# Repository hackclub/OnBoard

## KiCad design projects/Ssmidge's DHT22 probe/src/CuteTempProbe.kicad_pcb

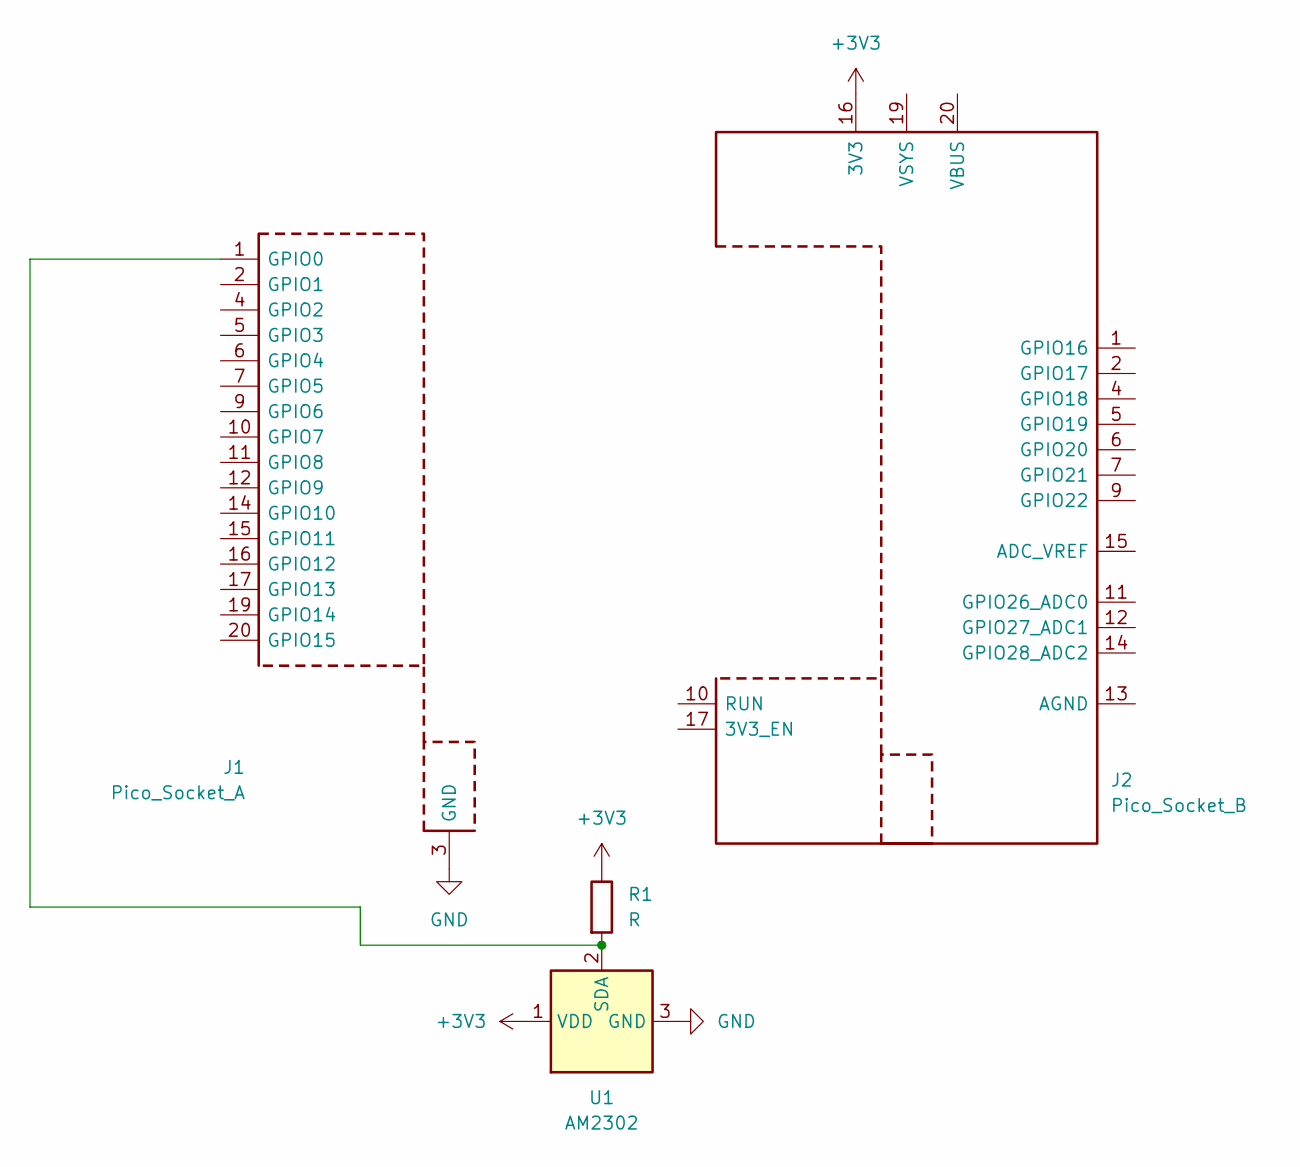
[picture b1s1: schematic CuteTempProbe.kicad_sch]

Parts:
J1: Pico_Socket_A; RaspberryPi_Pico_PinSocket_1x20_P2.54mm_Vertical
J2: Pico_Socket_B; RaspberryPi_Pico_PinSocket_1x20_P2.54mm_Vertical
R1: R; R_0201_0603Metric
U1: AM2302; ASAIR_AM2302_P2.54mm_Vertical

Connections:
+3V3: J2.16 (3V3), R1.1, U1.1 (VDD)
GND: J1.3 (GND), J1.8 (GND), J1.13 (GND), J1.18 (GND), U1.3 (GND), U1.4 (GND)
unnamed: J1.1 (GPIO0), R1.2, U1.2 (SDA)
unnamed: J2.3 (GND), J2.8 (GND), J2.18 (GND)

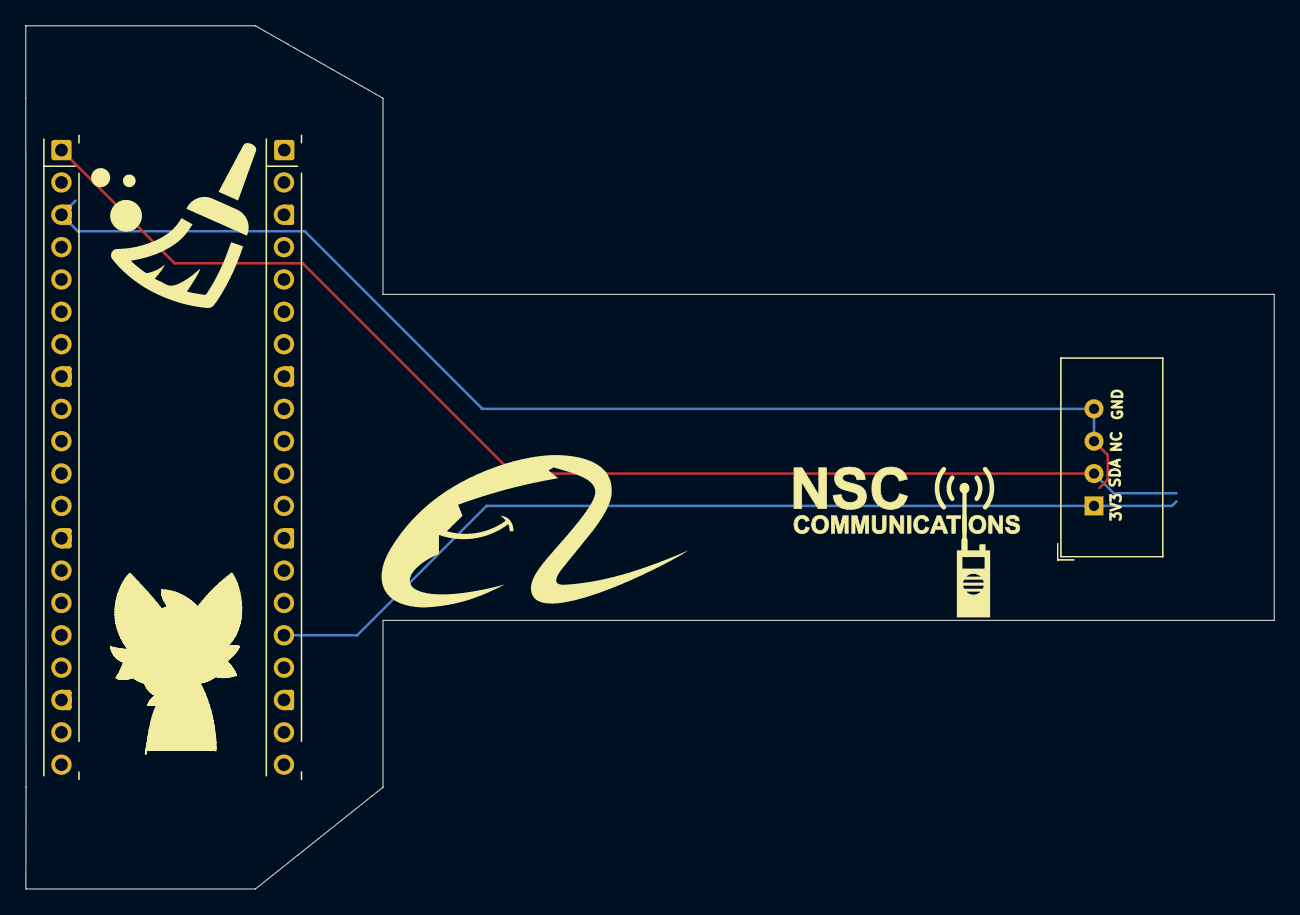
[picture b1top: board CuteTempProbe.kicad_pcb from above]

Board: 2 copper layers, 98.0 x 67.8 mm, 4 parts (1 on the bottom side), 4 nets.

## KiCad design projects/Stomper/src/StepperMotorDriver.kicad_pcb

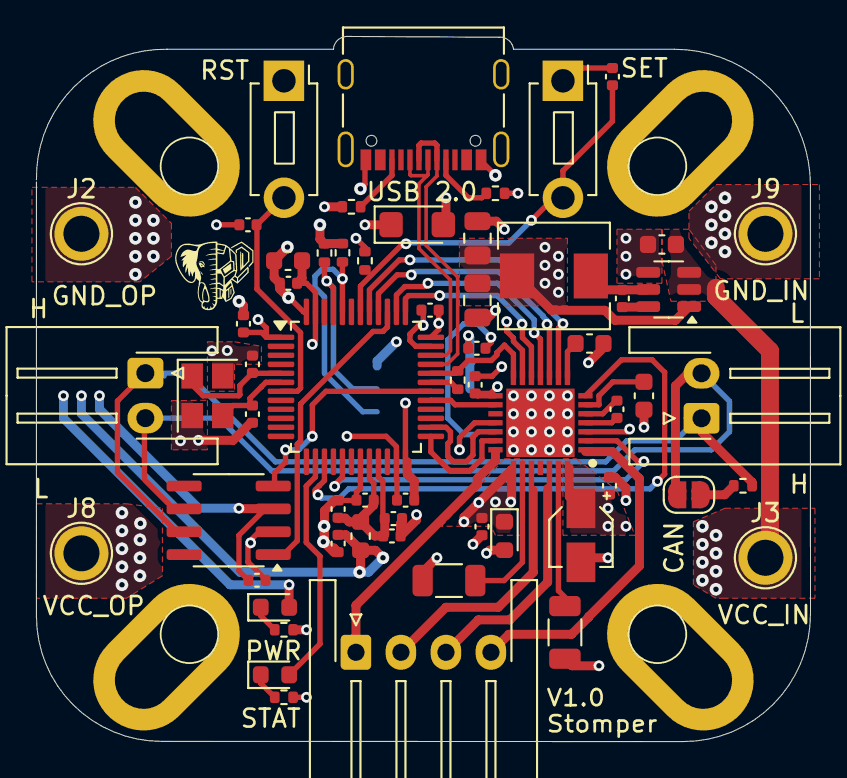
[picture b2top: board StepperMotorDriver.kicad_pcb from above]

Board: 4 copper layers, 43.0 x 39.2 mm, 65 parts (1 on the bottom side), 45 nets.

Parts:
C1: .1uF; C_0402_1005Metric
C2, C5, C7, C9, C26: 100nF; C_0402_1005Metric
C3, C4: 10pF; C_0402_1005Metric
C6: 22nF 50V; C_0402_1005Metric
C8: 100uF; CP_Elec_3x5.3
C10: 100n 16V; C_0603_1608Metric
C11: 2.2uF 6.3V; C_0603_1608Metric
C12, C13, C14, C16, C21: 100n; C_0402_1005Metric
C15: 10u; C_0603_1608Metric
C17: 10n; C_0402_1005Metric
C18, C19, C22: 1u; C_0402_1005Metric
C20, C23: 0.1u; C_0402_1005Metric
C25: 10uF; C_0603_1608Metric
C27, C28: 22uF; C_0805_2012Metric
D1: SMF6V0A; D_SMF
D2: D_TVS_30V; D_0603_1608Metric
D3: Green; LED_0603_1608Metric
D4: Red; LED_0603_1608Metric
FB3: 120R; L_0603_1608Metric
H1, H2, H3, H4: MountingHole_Pad; MountingHole_3.2mm_M3_DIN965_Pad
IC2: TMC2209-LA; QFN50P500X500X90-29N
J1, J7: Conn_01x02_Pin; JST_XH_S2B-XH-A-1_1x02_P2.50mm_Horizontal
J2, J3, J8, J9: Conn_01x01_Pin; TestPoint_Plated_Hole_D2.0mm
J4: Conn_01x04_Socket; JST_XH_S4B-XH-A-1_1x04_P2.50mm_Horizontal
J10: USB_C_Receptacle_USB2.0_16P; USB_C_Receptacle_Palconn_UTC16-G
JP1: Jumper_2_Bridged; SolderJumper-2_P1.3mm_Open_RoundedPad1.0x1.5mm
L2: 4.7uF; L_Chilisin_BMRA00050530
R1, R10: 1k5; R_0402_1005Metric
R2, R3: 5.1k; R_0402_1005Metric
R4: R1k; R_0402_1005Metric
R5, R6: 100mOHM; R_1206_3216Metric
R7, R8: 5.1kOhm; R_0402_1005Metric
R9: 1.5k; R_0402_1005Metric
R11: 120R; R_0402_1005Metric
SW1, SW2: SW_SPST; SW_PUSH_1P1T_6x3.5mm_H5.0_APEM_MJTP1250
U2: SN65HVD232; SOIC-8_3.9x4.9mm_P1.27mm
U3: STM32G473CBTx; LQFP-48_7x7mm_P0.5mm
U5: AP63203WU; TSOT-23-6
U6: MT6701CT; SO-8_3.9x4.9mm_P1.27mm
Y2: 16MHz; Crystal_SMD_3225-4Pin_3.2x2.5mm

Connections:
+3.3VA: C17.1, C18.1, C21.1, C22.1, FB3.1, U3.20 (VREF+), U3.21 (VDDA)
+3V3: C1.1, C2.1, C5.1, C12.1, C13.1, C14.1, C15.1, C16.1, C19.1, C27.1, C28.2, D1.1 (A1), D3.2 (A), FB3.2, IC2.15 (VCC_IO), L2.2, R1.1, R2.2, R3.2, U2.3 (VCC), U3.1 (VBAT), U3.24 (VDD), U3.36 (VDD), U3.48 (VDD), U5.1 (FB), U6.1 (VDD), U6.2 (MODE), U6.8 (Z)
/CANH: J1.1, J7.1, R11.2, U2.7 (CANH)
/CANL: J1.2, J7.2, JP1.1 (A), U2.6 (CANL)
/CAN_RX: U2.4 (R), U3.30 (PA8)
/CAN_TX: U2.1 (D), U3.39 (PA15)
/ESCL: R2.1, U3.45 (PB8), U6.7 (B)
/ESDA: R3.1, U3.44 (PB7), U6.6 (A)
/MOT_DIAG: IC2.11 (DIAG), U3.38 (PA14)
/MOT_DIR: IC2.19 (DIR), U3.26 (PB12)
/MOT_ENABLE: IC2.2 (ENN), U3.17 (PB1)
/MOT_INDEX: IC2.12 (INDEX), U3.37 (PA13)
/MOT_MS1: IC2.9 (MS1_AD0), U3.41 (PB4)
/MOT_MS2: IC2.10 (MS2_AD1), U3.40 (PB3)
/MOT_SPREAD: IC2.7 (SPREAD), U3.15 (PA7)
/MOT_STBY: IC2.20 (STDBY), U3.25 (PB11)
/MOT_STEP: IC2.16 (STEP), U3.29 (PB15)
/MOT_UART_RX: IC2.14 (PDN_UART), R4.1, U3.32 (PA10)
/MOT_UART_TX: R4.2, U3.31 (PA9)
/OA1: IC2.24 (OA1), J4.2
/OA2: IC2.21 (OA2), J4.1
/OB1: IC2.26 (OB1), J4.3
/OB2: IC2.1 (OB2), J4.4
/USB_D+: J10.A6 (D+), J10.B6 (D+), U3.34 (PA12)
/USB_D-: J10.A7 (D-), J10.B7 (D-), U3.33 (PA11)
GND: C1.2, C2.2, C3.2, C4.2, C5.2, C7.2, C8.2, C9.2, C11.1, C12.2, C13.2, C14.2, C15.2, C16.2, C17.2, C18.2, C19.2, C20.1, C21.2, C22.2, C23.2, C25.1, C27.2, C28.1, D1.2 (A2), D2.2 (A), H1.1, H2.1, H3.1, H4.1, IC2.3 (GND_1), IC2.13 (CLK), IC2.18 (GND_2), IC2.29 (EP), J2.1, J9.1, J10.A1 (GND), J10.A12 (GND), J10.B1 (GND), J10.B12 (GND), J10.S1 (SHIELD), R5.1, R6.1, R7.2, R8.2, R9.2, R10.2, SW1.1 (A), SW2.1 (A), U2.2 (GND), U3.19 (VSSA), U3.23 (VSS), U3.35 (VSS), U3.47 (VSS), U5.4 (GND), U6.4 (GND), Y2.2, Y2.4
unnamed: D3.1 (K), R9.1
unnamed: D4.2 (A), U3.14 (PA6)
unnamed: D4.1 (K), R10.1
unnamed: C11.2, IC2.8 (5VOUT)
unnamed: IC2.23 (BRA), R6.2
unnamed: IC2.27 (BRB), R5.2
unnamed: C6.2, IC2.5 (CPI)
unnamed: C6.1, IC2.4 (CPO)
unnamed: C10.2, IC2.6 (VCP)
unnamed: J10.A5 (CC1), R7.1
unnamed: J10.B5 (CC2), R8.1
unnamed: JP1.2 (B), R11.1
unnamed: C23.1, R1.2, SW1.2 (B), U3.42 (PB5)
unnamed: C20.2, SW2.2 (B), U3.7 (PG10)
unnamed: C3.1, U3.5 (PF0), Y2.1
unnamed: C4.1, U3.6 (PF1), Y2.3
unnamed: C26.2, U5.6 (BST)
unnamed: C26.1, L2.1, U5.5 (SW)
VCC: C7.1, C8.1, C9.1, C10.1, C25.2, D2.1 (K), IC2.22 (VS_1), IC2.28 (VS_2), J3.1, J8.1, U5.2 (EN), U5.3 (IN)

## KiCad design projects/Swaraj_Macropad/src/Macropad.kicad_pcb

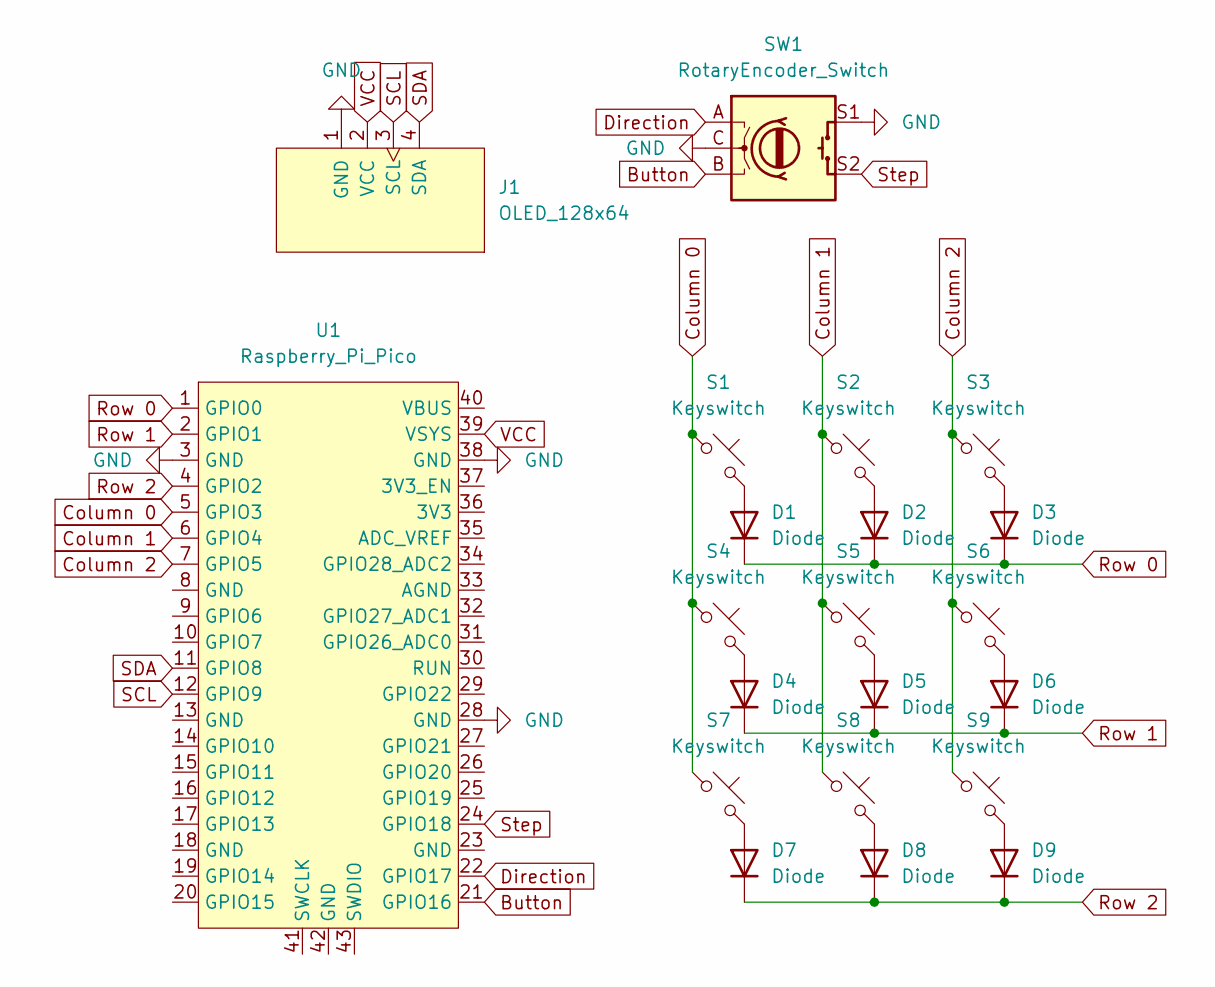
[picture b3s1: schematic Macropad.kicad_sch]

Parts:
D1, D2, D3, D4, D5, D6, D7, D8, D9: Diode; Diode_DO-35
J1: OLED_128x64
S1, S2, S3, S4, S5, S6, S7, S8, S9: Keyswitch; MX_PCB_1.00u
SW1: RotaryEncoder_Switch; RotaryEncoder_Alps_EC11E-Switch_Vertical_H20mm
U1: Raspberry_Pi_Pico

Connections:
Button: SW1.B, U1.21 (GPIO16)
Column 0: S1.1, S4.1, S7.1, U1.5 (GPIO3)
Column 1: S2.1, S5.1, S8.1, U1.6 (GPIO4)
Column 2: S3.1, S6.1, S9.1, U1.7 (GPIO5)
Direction: SW1.A, U1.22 (GPIO17)
GND: J1.1 (GND), SW1.C, SW1.S1, U1.3 (GND), U1.28 (GND), U1.38 (GND)
unnamed: D1.2 (A), S1.2
unnamed: D2.2 (A), S2.2
unnamed: D3.2 (A), S3.2
unnamed: D4.2 (A), S4.2
unnamed: D5.2 (A), S5.2
unnamed: D6.2 (A), S6.2
unnamed: D7.2 (A), S7.2
unnamed: D8.2 (A), S8.2
unnamed: D9.2 (A), S9.2
Row 0: D1.1 (K), D2.1 (K), D3.1 (K), U1.1 (GPIO0)
Row 1: D4.1 (K), D5.1 (K), D6.1 (K), U1.2 (GPIO1)
Row 2: D7.1 (K), D8.1 (K), D9.1 (K), U1.4 (GPIO2)
SCL: J1.3 (SCL), U1.12 (GPIO9)
SDA: J1.4 (SDA), U1.11 (GPIO8)
Step: SW1.S2, U1.24 (GPIO18)
VCC: J1.2 (VCC), U1.39 (VSYS)

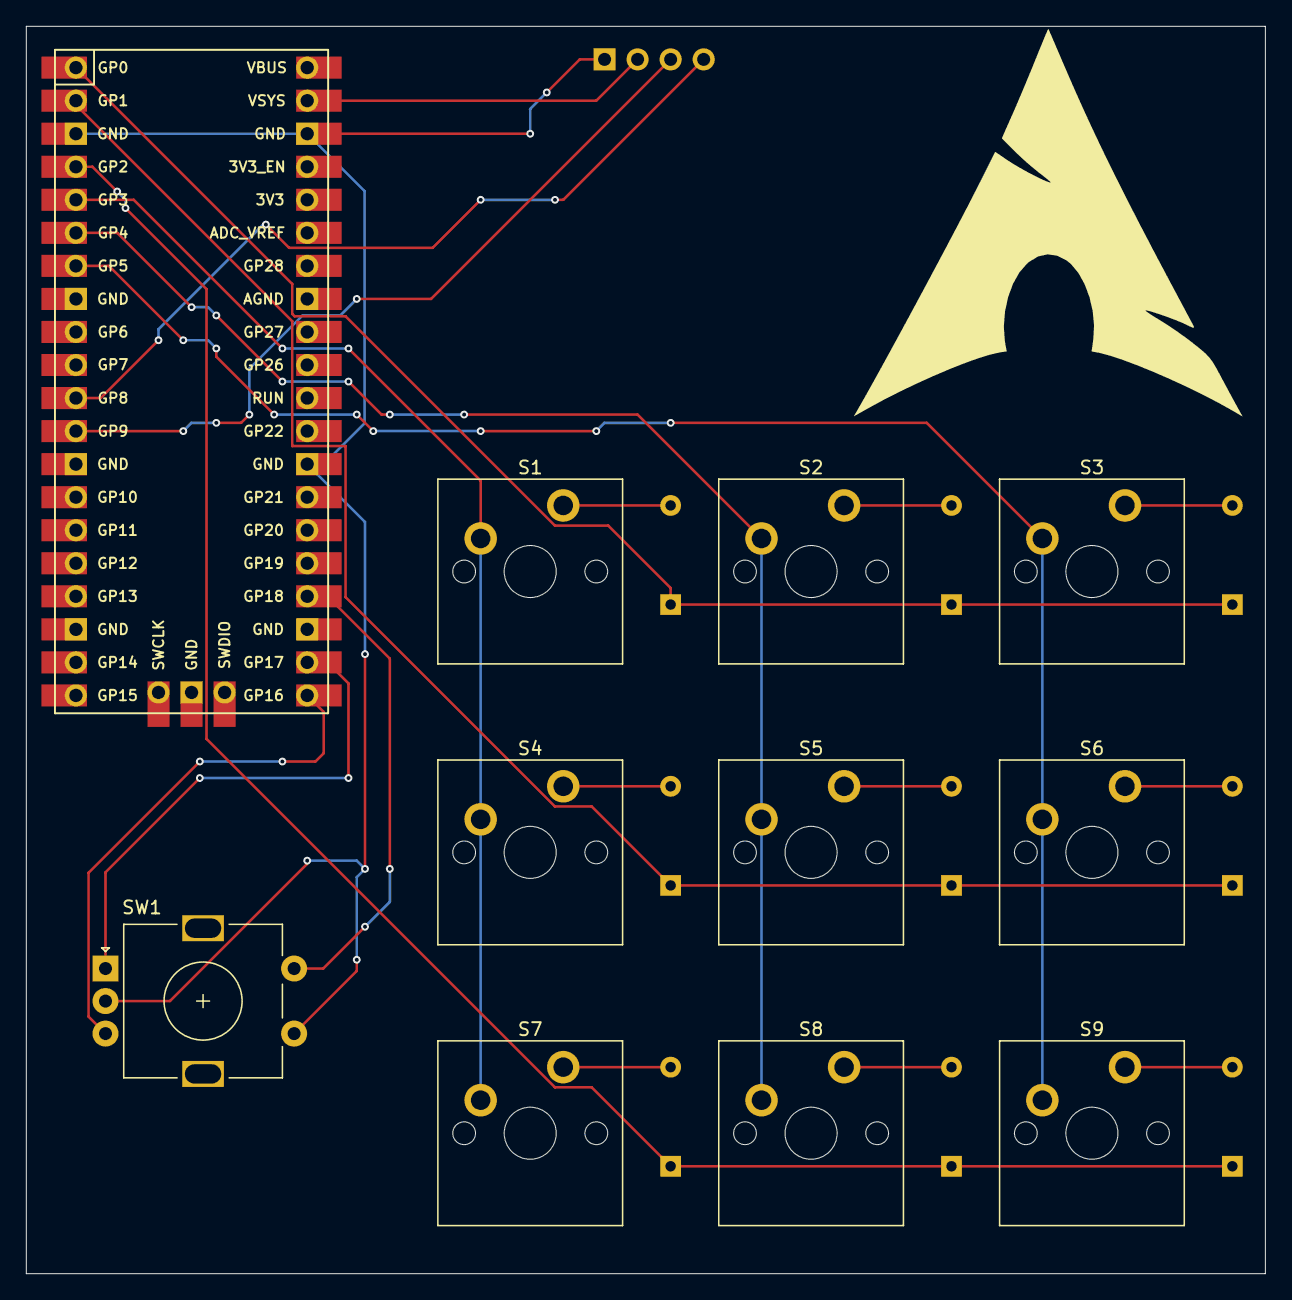
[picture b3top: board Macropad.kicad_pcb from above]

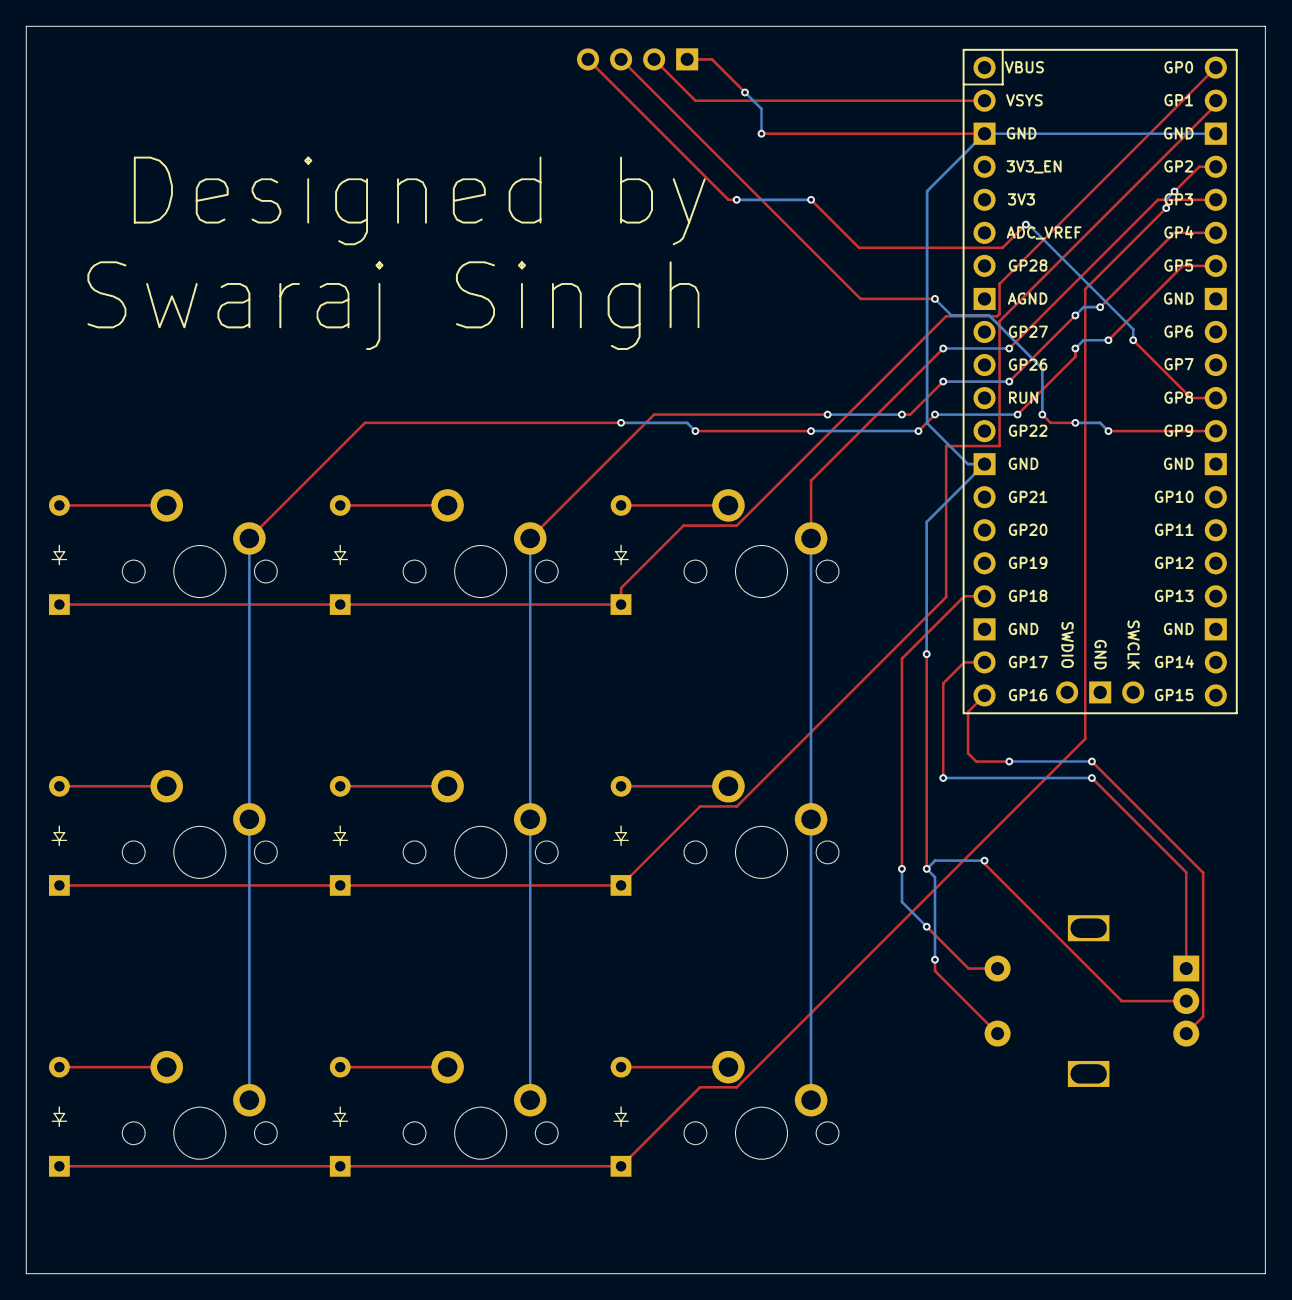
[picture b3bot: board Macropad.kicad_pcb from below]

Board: 2 copper layers, 95.2 x 95.9 mm, 21 parts (9 on the bottom side), 22 nets.

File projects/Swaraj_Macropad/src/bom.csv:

Designator,Footprint,Quantity,Value,LCSC Part #
"D1, D2, D3, D4, D5, D6, D7, D8, D9",Diode_DO-35,9,Diode,
J1,OLED_128x64,1,OLED_128x64,
"S1, S2, S3, S4, S5, S6, S7, S8, S9",MX_PCB_1.00u,9,Keyswitch,
SW1,RotaryEncoder_Alps_EC11E-Switch_Vertical_H20mm,1,RotaryEncoder_Switch,
U1,Raspberry_Pi_Pico,1,Raspberry_Pi_Pico,

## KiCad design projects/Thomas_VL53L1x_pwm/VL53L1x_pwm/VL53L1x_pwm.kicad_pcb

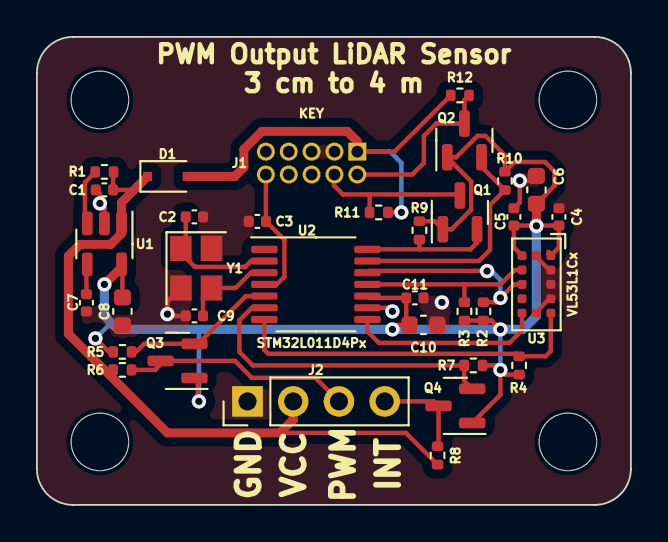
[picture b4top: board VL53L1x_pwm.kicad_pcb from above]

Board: 2 copper layers, 33.0 x 26.0 mm, 34 parts (0 on the bottom side), 21 nets.

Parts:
C1: 1 uF; C_0402_1005Metric
C2, C9: 10 pF; C_0402_1005Metric
C3, C4, C5, C11: 0.1 uF; C_0402_1005Metric
C6, C8, C10: 4.7 uF; C_0603_1608Metric
C7: 10 nF; C_0402_1005Metric
D1: D_Schottky; D_SOD-323F
J1: Conn_02x05_Odd_Even; PinHeader_2x05_P1.27mm_Vertical
J2: Conn_01x04; PinHeader_1x04_P2.54mm_Vertical
Q1, Q2, Q3, Q4: BSS138; SOT-23
R1, R2, R3, R4, R5, R6, R7, R8, R9, R10, R11, R12: 10k; R_0402_1005Metric
U1: LP2985-1.8; SOT-23-5
U2: STM32L011D4Px; TSSOP-14_4.4x5mm_P0.65mm
U3: VL53L1CXV0FY1; ST_VL53L1x
Y1: 16 MHz 9 pF; Crystal_SMD_3225-4Pin_3.2x2.5mm

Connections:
+1V8: C4.1, C5.1, C6.1, C8.1, C10.2, C11.2, Q1.1 (G), Q2.1 (G), Q3.1 (G), Q4.1 (G), R2.2, R3.1, R4.1, R5.2, R7.2, R9.2, R10.2, U1.5 (VOUT), U2.10 (VDD), U3.1 (AVDDVCSEL), U3.11 (AVDD)
+3V3: D1.2 (A), J1.1, R11.1, R12.1
/CLK_A: C2.2, U2.2 (PC14), Y1.1
/CLK_B: C9.1, U2.3 (PC15), Y1.3
GND: C1.2, C2.1, C3.1, C4.2, C5.2, C6.2, C7.2, C8.2, C9.2, C10.1, C11.1, J1.3, J1.5, J1.9, J2.1, U1.2 (GND), U2.9 (VSS), U3.2 (AVSSVCSEL), U3.3 (GND), U3.4 (GND), U3.6 (GND), U3.12 (GND), Y1.2, Y1.4
INT: U2.8 (PA7), U3.7 (GPIO1)
INTOUT: J2.4, Q4.3 (D), R8.2
INTOUT1V8: Q4.2 (S), R7.1, U2.6 (PA1)
unnamed: C7.1, U1.4 (BP)
unnamed: R1.2, U1.3 (ON/~OFF)
PWMOUT: J2.3, Q3.3 (D), R6.2
PWMOUT1V8: Q3.2 (S), R5.1, U2.5 (PA0)
RST: C3.2, J1.10, U2.4 (NRST)
SCL: R3.2, U2.11 (PA9), U3.10 (SCL)
SDA: R2.1, U2.12 (PA10), U3.9 (SDA)
SWCLK: J1.4, Q1.3 (D), R11.2
SWCLK1V8: Q1.2 (S), R9.1, U2.14 (PA14)
SWDIO: J1.2, Q2.3 (D), R12.2
SWDIO1V8: Q2.2 (S), R10.1, U2.13 (PA13)
VCC: C1.1, D1.1 (K), J2.2, R1.1, R6.1, R8.1, U1.1 (VIN)
XSHUT: R4.2, U2.7 (PA4), U3.5 (XSHUT)

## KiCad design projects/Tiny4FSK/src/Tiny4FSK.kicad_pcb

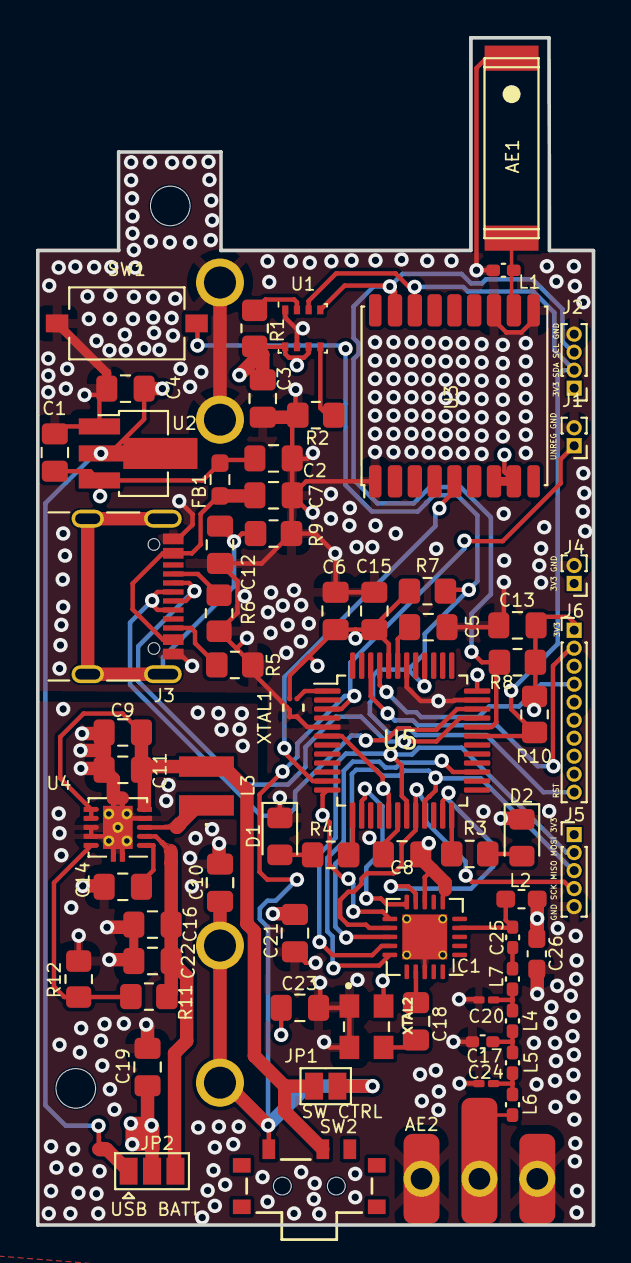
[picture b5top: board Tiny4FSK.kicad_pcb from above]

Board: 4 copper layers, 30.9 x 66.0 mm, 69 parts (1 on the bottom side), 46 nets.

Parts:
AE1: GPS ANT; GPS1003
AE2: ANT; Antenna_Whip
BT1: AAA; BAT_BK-82
C1, C3, C4, C5, C10, C19: 1uF; C_0805_2012Metric_Pad1.18x1.45mm_HandSolder
C2, C7: 100 nF (J1); C_0805_2012Metric_Pad1.18x1.45mm_HandSolder
C6, C11, C13, C14, C15, C21, C22: 100nF; C_0805_2012Metric_Pad1.18x1.45mm_HandSolder
C8, C9: 10uF; C_0805_2012Metric_Pad1.18x1.45mm_HandSolder
C12: 4.5 nF; C_0805_2012Metric_Pad1.18x1.45mm_HandSolder
C16: 22uF; C_0805_2012Metric_Pad1.18x1.45mm_HandSolder
C17: 12 pF; C_0402_1005Metric_Pad0.74x0.62mm_HandSolder
C18: 100 pF; C_0805_2012Metric_Pad1.18x1.45mm_HandSolder
C20: 15 pF; C_0201_0603Metric_Pad0.64x0.40mm_HandSolder
C23: 10 nF; C_0805_2012Metric_Pad1.18x1.45mm_HandSolder
C24: 10 pF; C_0201_0603Metric_Pad0.64x0.40mm_HandSolder
C25: 9.1 pF; C_0402_1005Metric_Pad0.74x0.62mm_HandSolder
C26: 100nF; C_0603_1608Metric_Pad1.08x0.95mm_HandSolder
D1: Success; LED_0805_2012Metric_Pad1.15x1.40mm_HandSolder
D2: Error; LED_0805_2012Metric_Pad1.15x1.40mm_HandSolder
FB1: BLM18AG121SN1D (J1); R_0603_1608Metric_Pad0.98x0.95mm_HandSolder
IC1: SI4063; QFN-20-1EP_4x4mm_P0.5mm_EP2.5x2.5mm_ThermalVias
J1: PWR Batt; PinHeader_1x02_P1.00mm_Vertical
J2: I2C; PinHeader_1x04_P1.00mm_Vertical
J3: USBC; USB_C_Receptacle_GCT_USB4105-xx-A_16P_TopMnt_Horizontal
J4: PWR Supply; PinHeader_1x02_P1.00mm_Vertical
J5: SPI; PinHeader_1x05_P1.00mm_Vertical
J6: JTAG; PinHeader_1x10_P1.00mm_Vertical
JP1: SWITCH_EN; SolderJumper-2_P1.3mm_Open_Pad1.0x1.5mm
JP2: SOURCE; SolderJumper-3_P1.3mm_Open_Pad1.0x1.5mm
L1, L7: 33 nH; L_0402_1005Metric_Pad0.77x0.64mm_HandSolder
L2: 220 nH; L_0603_1608Metric_Pad1.05x0.95mm_HandSolder
L3: 2.2uH; LPS3015222MRB
L4: 30 nH; L_0402_1005Metric_Pad0.77x0.64mm_HandSolder
L5: 36 nH; L_0402_1005Metric_Pad0.77x0.64mm_HandSolder
L6: 22 nH; L_0402_1005Metric_Pad0.77x0.64mm_HandSolder
R1, R2, R12: 10k; R_0805_2012Metric_Pad1.20x1.40mm_HandSolder
R3, R4: 100; R_0805_2012Metric_Pad1.20x1.40mm_HandSolder
R5, R6: 5k1; R_0805_2012Metric_Pad1.20x1.40mm_HandSolder
R7: 220; R_0805_2012Metric_Pad1.20x1.40mm_HandSolder
R8, R10: 1.8k; R_0805_2012Metric_Pad1.20x1.40mm_HandSolder
R9: 1M; R_0805_2012Metric_Pad1.20x1.40mm_HandSolder
R11: 56k; R_0805_2012Metric_Pad1.20x1.40mm_HandSolder
SW1: RST; SW_Tactile_SPST_NO_Straight_CK_PTS636Sx25SMTRLFS
SW2: BATT PWR; WS-SLSU_6p7x2p7_WRE
U1: BME280; Bosch_LGA-8_2.5x2.5mm_P0.65mm_ClockwisePinNumbering
U2: Linear Step-Down; SOT-89-3_Handsoldering
U3: MAX-M10S; ublox_MAX
U4: TPS61200DRC; Texas_S-PVSON-N10_ThermalVias
U5: ATSAMD21G18A-A; TQFP-48_7x7mm_P0.5mm
XTAL1: TCXO MCU; BGA4_SiT1532_SIT
XTAL2: OSC_ECS-TXO-32CSMV-260-AN-TR

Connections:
+3.3V: C3.1, C6.1, C8.1, C13.1, C15.2, C19.1, C21.1, C23.2, C26.2, IC1.6 (VDD_1), IC1.8 (VDD_2), J2.1, J4.1, J5.1, J6.1, JP2.2 (B), L2.1, R1.1, R7.2, R8.2, R10.2, U1.6 (VDDIO), U1.8 (VDD), U3.7 (VCC_IO), U3.8 (VCC), U5.6 (VDDANA), U5.17 (VDDIO), U5.36 (VDDIO), U5.44 (VDDIN), XTAL1.3 (VDD), XTAL2.4 (VDD)
ANT_GPS: AE1.2 (PCB_Trace), L1.2, U3.11 (RF_IN)
BATT_SENSE: BT1.+, C10.1, J1.1, JP1.2 (B), SW2.1 (A), U5.3 (PA02)
BOOST: C16.1, C22.1, JP2.3 (C), R11.1, U4.2 (VOUT)
BST_IN: C9.1, C11.1, JP1.1 (A), L3.2, SW2.2 (B), U4.5 (VIN), U4.6 (EN), U4.7 (UVLO)
D+: J3.A6 (D+), J3.B6 (D+), U5.34 (PA25)
D-: J3.A7 (D-), J3.B7 (D-), U5.33 (PA24)
ERROR: R3.1, U5.24 (PA15)
EXTINT: U3.5 (EXTINT), U5.11 (PA06)
Earth: AE1.1 (FEED), AE2.2 (Shield), BT1.-, C1.1, C2.2, C3.2, C4.2, C5.2, C6.2, C7.2, C8.2, C9.2, C10.2, C11.2, C12.1, C13.2, C14.2, C15.1, C16.2, C17.2, C19.2, C20.2, C21.2, C22.2, C23.1, C24.2, C26.1, D1.1 (K), D2.1 (K), IC1.18 (GND_1), IC1.21 (GND_2), J1.2, J2.4, J3.A1 (GND), J3.A12 (GND), J3.B1 (GND), J3.B12 (GND), J4.2, J5.5, J6.3, J6.5, L1.1, R2.2, R5.1, R6.1, R9.2, R12.2, SW1.1, U1.1 (GND), U1.7 (GND), U2.1 (GND), U3.1 (GND), U3.10 (GND), U3.12 (GND), U4.4 (PGND), U4.8 (PS), U4.9 (GND), U4.11 (PAD), U5.5 (GNDANA), U5.18 (GND), U5.35 (GND), U5.42 (GND), XTAL1.1 (GND), XTAL1.4 (GND), XTAL2.1 (GND), XTAL2.2 (GND)
GPIO0: IC1.9 (GPIO0), U5.23 (PA14)
GPIO1: IC1.10 (GPIO1), U5.14 (PA09)
LDO: C4.1, JP2.1 (A), U2.2 (VO)
LIN: C1.2, C2.1, FB1.2, U2.3 (VI)
MISO: IC1.13 (SDO), J5.3, U5.21 (PA12)
MOSI: IC1.14 (SDI), J5.2, U5.19 (PB10)
unnamed: AE2.1 (RF), L6.2
unnamed: C17.1, L4.2, L5.1
unnamed: C20.1, L4.1, L7.2
unnamed: C24.1, L5.2, L6.1
unnamed: C25.2, L7.1
unnamed: D1.2 (A), R4.1
unnamed: D2.2 (A), R3.2
unnamed: C18.2, IC1.17 (XIN)
unnamed: J3.A5 (CC1), R6.2
unnamed: J3.B5 (CC2), R5.2
unnamed: C12.2, J3.S1 (SHIELD), R9.1
unnamed: R1.2, U1.2 (CSB)
unnamed: R2.1, U1.5 (SDO)
unnamed: R11.2, R12.1, U4.10 (FB)
unnamed: L3.1, U4.3 (L)
unnamed: C14.1, U4.1 (VAUX)
unnamed: U5.1 (PA00), XTAL1.2 (CLK_OUT)
unnamed: C5.1, U5.43 (VDDCORE)
RF_ANT: C25.1, IC1.4 (TX), L2.2
RF_RST: IC1.11 (NIRQ), U5.12 (PA07)
RF_SS: IC1.15 (NSEL), U5.27 (PA18)
RF_XO: C18.1, XTAL2.3 (CLK_OUT)
SCK: IC1.12 (SCLK), J5.4, U5.20 (PB11)
SCL: J2.3, R8.1, U1.4 (SCK), U3.17 (SCL), U5.32 (PA23)
SDA: J2.2, R10.1, U1.3 (SDI), U3.16 (SDA), U5.31 (PA22)
SUCCESS: R4.2, U5.13 (PA08)
SWCLK: J6.4, U5.45 (PA30)
SWDIO: J6.2, U5.46 (PA31)
USB: C7.1, FB1.1, J3.A4 (VBUS), J3.A9 (VBUS), J3.B4 (VBUS), J3.B9 (VBUS)
nRST: J6.10, R7.1, SW1.2, U5.40 (~RESET)

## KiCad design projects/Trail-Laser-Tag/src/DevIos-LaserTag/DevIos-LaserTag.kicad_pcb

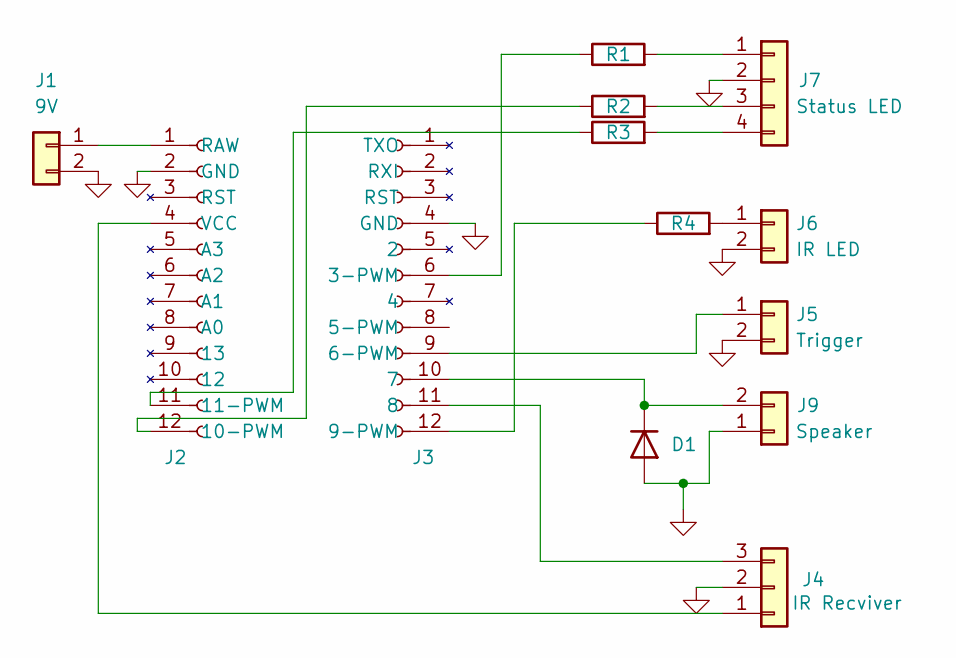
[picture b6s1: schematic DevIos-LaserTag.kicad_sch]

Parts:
D1: SS14; D_SMA; LCSC Part # C2480
J1: 9V; PinHeader_1x02_P2.54mm_Vertical; LCSC Part # C5360898
J2, J3: Conn_01x12_Female; PinSocket_1x12_P2.54mm_Vertical; LCSC Part # C5224029
J4: IR Recviver; PinHeader_1x03_P2.54mm_Vertical; LCSC Part # C49257
J5: Trigger; PinHeader_1x02_P2.54mm_Vertical; LCSC Part # C5360898
J6: IR LED; PinHeader_1x02_P2.54mm_Vertical; LCSC Part # C5360898
J7: Status LED; PinHeader_1x04_P2.54mm_Vertical; LCSC Part # C5116483
J9: Speaker; PinHeader_1x02_P2.54mm_Vertical; LCSC Part # C5360898
R1, R2, R3, R4: 1k; R_0805_2012Metric; LCSC Part # C17513

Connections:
GND: D1.2 (A), J1.2, J2.2 (GND), J3.4 (GND), J4.2, J5.2, J6.2, J7.2, J9.1
unnamed: D1.1 (K), J3.10 (7), J9.2
unnamed: J1.1, J2.1 (RAW)
unnamed: J2.12 (10-PWM), R2.1
unnamed: J2.11 (11-PWM), R3.1
unnamed: J2.4 (VCC), J4.1
unnamed: J3.6 (3-PWM), R1.1
unnamed: J3.9 (6-PWM), J5.1
unnamed: J3.11 (8), J4.3
unnamed: J3.12 (9-PWM), R4.1
unnamed: J6.1, R4.2
unnamed: J7.1, R1.2
unnamed: J7.3, R2.2
unnamed: J7.4, R3.2

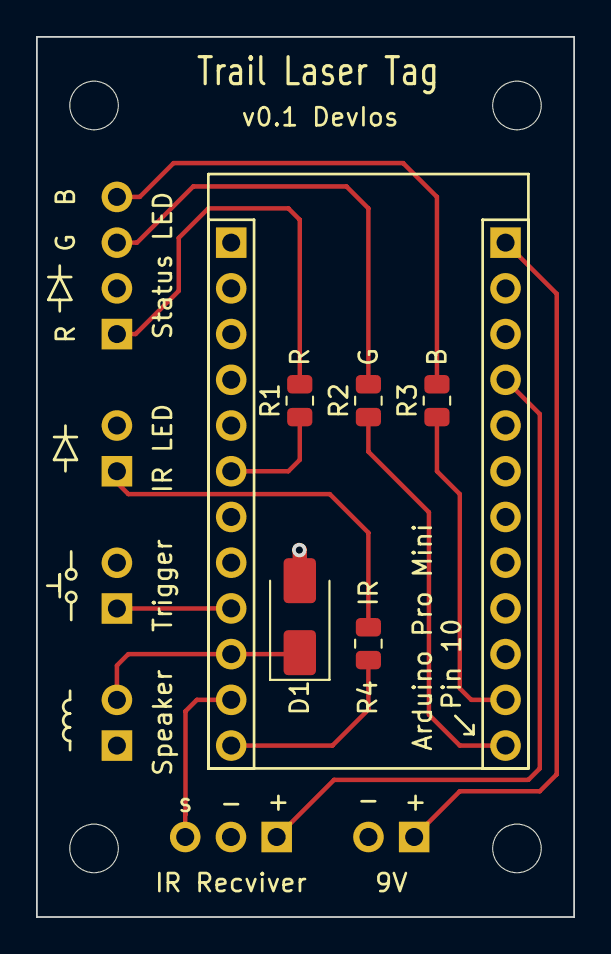
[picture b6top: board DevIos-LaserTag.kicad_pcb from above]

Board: 2 copper layers, 29.8 x 48.9 mm, 13 parts (0 on the bottom side), 14 nets.

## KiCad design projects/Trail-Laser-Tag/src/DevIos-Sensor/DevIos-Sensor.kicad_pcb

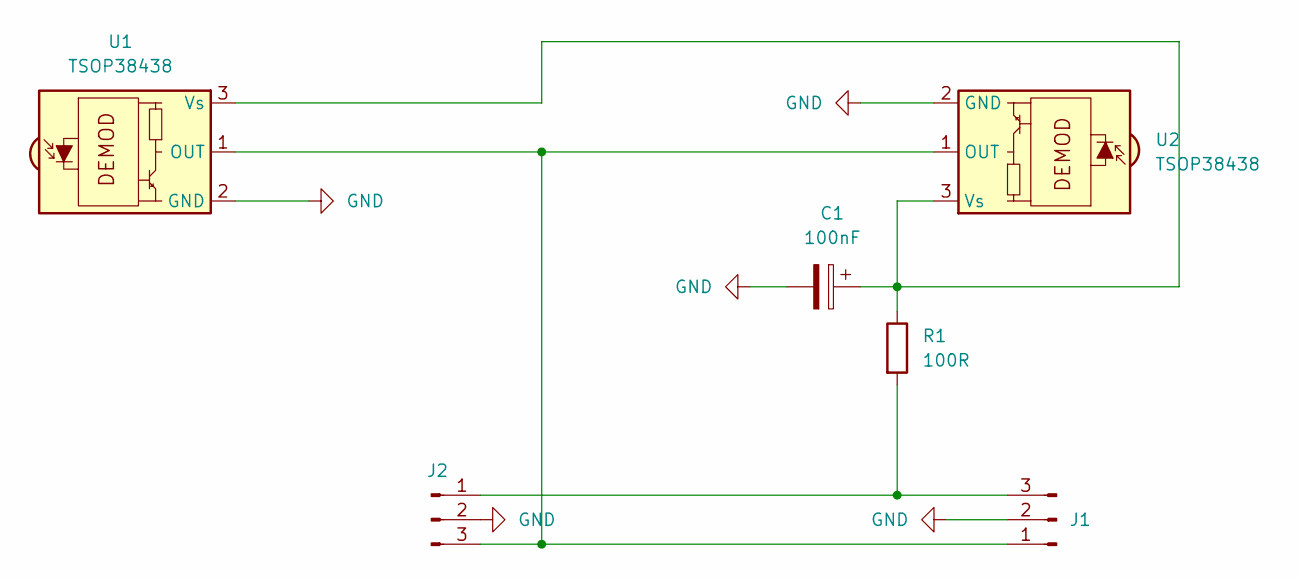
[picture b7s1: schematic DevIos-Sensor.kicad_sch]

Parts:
C1: 100nF; C_0805_2012Metric; LCSC Part Number C28233
J1, J2: Conn_01x03_Male; SolderWire-0.1sqmm_1x03_P3.6mm_D0.4mm_OD1mm_Relief
R1: 100R; R_0805_2012Metric; LCSC Part Number C17408
U1, U2: TSOP38438; Vishay_MINICAST-3Pin; LCSC Part Number C145271

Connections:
GND: C1.2, J1.2, J2.2, U1.2 (GND), U2.2 (GND)
unnamed: J1.1, J2.3, U1.1 (OUT), U2.1 (OUT)
unnamed: J1.3, J2.1, R1.2
unnamed: C1.1, R1.1, U1.3 (Vs), U2.3 (Vs)

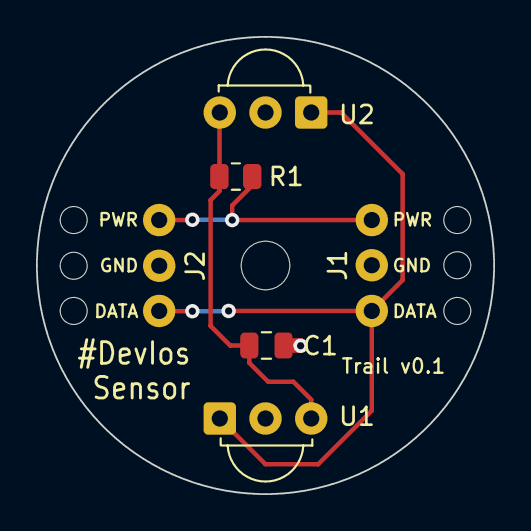
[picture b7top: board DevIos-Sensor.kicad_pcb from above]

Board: 2 copper layers, 25.4 x 25.4 mm, 6 parts (0 on the bottom side), 4 nets.

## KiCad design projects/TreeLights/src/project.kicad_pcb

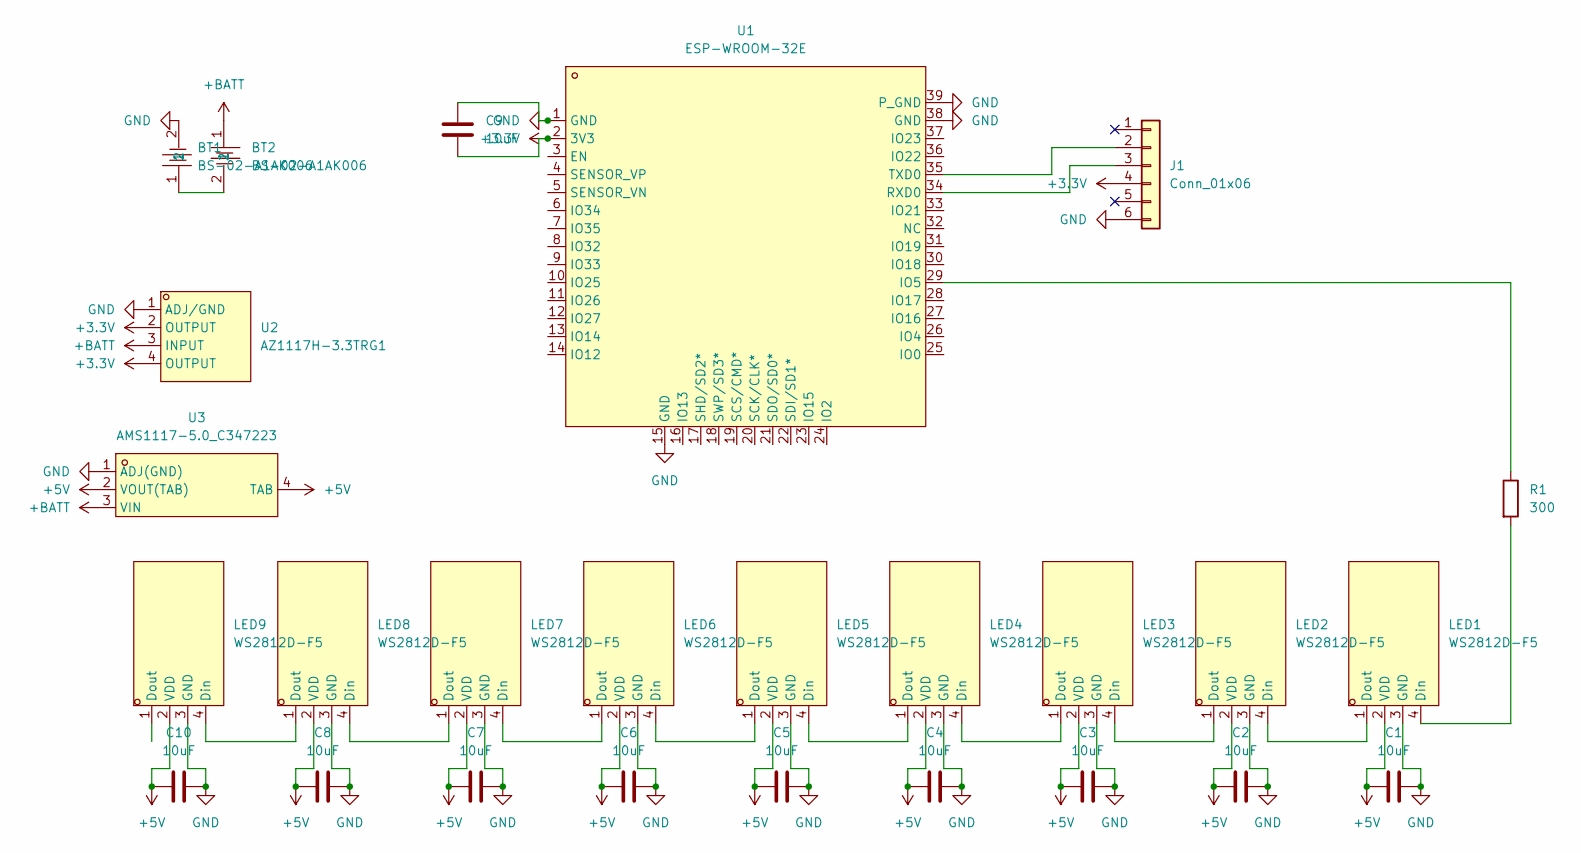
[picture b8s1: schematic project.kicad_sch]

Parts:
BT1, BT2: BS-02-A1AK006; BAT-TH_BS-02-A1AK006; LCSC Part C964746
C1, C2, C3, C4, C5, C6, C7, C8, C9, C10: 10uF; C_0603_1608Metric; LCSC C19702
J1: Conn_01x06; PinSocket_1x06_P2.54mm_Vertical
LED1, LED2, LED3, LED4, LED5, LED6, LED7, LED8, LED9: WS2812D-F5; LED-TH_4P-BD5.8-P1.30; LCSC Part C190565
R1: 300; R_0603_1608Metric; LCSC C114617
U1: ESP-WROOM-32E; COMM-SMD_ESP-WROOM-32D; LCSC Part C19949066
U2: AZ1117H-3.3TRG1; SOT-223-3_L6.5-W3.4-P2.30-LS7.0-BR; LCSC Part C110474
U3: AMS1117-5.0_C347223; SOT-223_L6.7-W3.5-P2.30-BR; LCSC Part C347223

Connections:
+3.3V: C9.1, J1.4, U1.2 (3V3), U2.2 (OUTPUT), U2.4 (OUTPUT)
+5V: C1.1, C2.1, C3.1, C4.1, C5.1, C6.1, C7.1, C8.1, C10.1, LED1.2 (VDD), LED2.2 (VDD), LED3.2 (VDD), LED4.2 (VDD), LED5.2 (VDD), LED6.2 (VDD), LED7.2 (VDD), LED8.2 (VDD), LED9.2 (VDD), U3.2 (VOUT(TAB)), U3.4 (TAB)
+BATT: BT2.1, U2.3 (INPUT), U3.3 (VIN)
GND: BT1.2, C1.2, C2.2, C3.2, C4.2, C5.2, C6.2, C7.2, C8.2, C9.2, C10.2, J1.6, LED1.3 (GND), LED2.3 (GND), LED3.3 (GND), LED4.3 (GND), LED5.3 (GND), LED6.3 (GND), LED7.3 (GND), LED8.3 (GND), LED9.3 (GND), U1.1 (GND), U1.15 (GND), U1.38 (GND), U1.39 (P_GND), U2.1 (ADJ/GND), U3.1 (ADJ(GND))
unnamed: BT1.1, BT2.2
unnamed: J1.2, U1.35 (TXD0)
unnamed: J1.3, U1.34 (RXD0)
unnamed: LED1.4 (Din), R1.2
unnamed: LED1.1 (Dout), LED2.4 (Din)
unnamed: LED2.1 (Dout), LED3.4 (Din)
unnamed: LED3.1 (Dout), LED4.4 (Din)
unnamed: LED4.1 (Dout), LED5.4 (Din)
unnamed: LED5.1 (Dout), LED6.4 (Din)
unnamed: LED6.1 (Dout), LED7.4 (Din)
unnamed: LED7.1 (Dout), LED8.4 (Din)
unnamed: LED8.1 (Dout), LED9.4 (Din)
unnamed: R1.1, U1.29 (IO5)
